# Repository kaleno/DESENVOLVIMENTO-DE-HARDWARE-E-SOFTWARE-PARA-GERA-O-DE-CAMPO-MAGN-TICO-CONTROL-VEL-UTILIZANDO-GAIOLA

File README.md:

# DESENVOLVIMENTO DE HARDWARE E SOFTWARE PARA GERAÇÃO DE CAMPO MAGNÉTICO CONTROLÁVEL

Este repositório contém o trabalho de desenvolvimento de hardware e software realizado no âmbito do Laboratório de Controle e Simulação de Sistemas Aeroespaciais (LODESTAR) da Universidade de Brasília (UnB). O objetivo principal é criar uma plataforma com interface gráfica para a geração de campo magnético controlável, direcionada para aplicações no simulador de pequenos satélites do LODESTAR.

## Visão Geral

O sistema atual do laboratório inclui uma gaiola de Helmholtz com dois pares de bobinas por eixo, uma estação de trabalho e fontes de tensão controláveis. Este projeto propõe atualizações e o desenvolvimento de novas funcionalidades para a plataforma existente.

Algumas das aplicações planejadas são:

- Reprodução do campo magnético em malha fechada utilizando o modelo International Geomagnetic Reference Field (IGRF) em conjunto com o propagador de órbita Simplified General Perturbations (SGP4).
- Reprodução dos vetores de campo magnético coletados pelos sensores do satélite AlfaCrux, recentemente lançado.
- Realização de testes preliminares para validar o novo sistema no contexto dos projetos em andamento no LODESTAR.

## Estrutura do Repositório

O repositório está organizado da seguinte forma:

- `Firmware_Circuito_Inversor/`: Contém os arquivos relacionados ao firmware do circuito inversor.
- `Outros/`: Diretório para outros arquivos relevantes.
- `PonteH/`: Contém os arquivos relacionados à ponte H.
- `PonteH2.0/`: Contém os arquivos relacionados à versão 2.0 da ponte H.
- `Software_Gaiola/`: Contém os arquivos relacionados ao software da gaiola de Helmholtz.
- `Manual_Gaiola_de_Helmholtz_(1).pdf`: Documento PDF contendo o manual da gaiola de Helmholtz.
- `README.md`: Este arquivo README com informações sobre o projeto.
- `TCC_ThiagoHenriqueFerreiradaSilva_biblioteca.pdf`: Documento PDF contendo o TCC (Trabalho de Conclusão de Curso) intitulado "DESENVOLVIMENTO DE HARDWARE E SOFTWARE PARA GERAÇÃO DE CAMPO MAGNÉTICO CONTROLÁVEL".

Certifique-se de ajustar os nomes dos diretórios e arquivos de acordo com a estrutura do seu repositório.

## Pré-requisitos e Instalação

1. Certifique-se de ter os seguintes componentes presentes no arquivo requirements.bat

2. Clone este repositório em sua máquina local usando o seguinte comando:

**git clone https://github.com/seu-usuario/nome-do-repositorio.git**

3. Navegue até o diretório clonado.

4. Siga as instruções específicas contidas em `Manual_Gaiola_de_Helmholtz_(1).pdf` para configurar e instalar as respectivas partes do sistema.

## Utilização

1. Certifique-se de que o hardware está corretamente configurado e conectado à sua estação de trabalho.

2. Inicie o software e abra a interface gráfica do sistema.

3. Utilize as funcionalidades disponíveis para gerar o campo magnético controlável de acordo com suas necessidades.

4. Consulte a documentação disponível em `docs/` para obter informações adicionais sobre a utilização do sistema.

## Contribuição

Se você deseja contribuir para este projeto, sinta-se à vontade para enviar um pull request com suas melhorias. Toda contribuição é bem-vinda!

## Licença

Este projeto é licenciado sob a MIT. Consulte o arquivo LICENSE para obter mais informações.

## Contato

Para mais informações sobre este projeto, entre em contato conosco:

- Nome: Thiago Henrique Ferreira da Silva
- E-mail: thiago.henriquef@hotmail.com

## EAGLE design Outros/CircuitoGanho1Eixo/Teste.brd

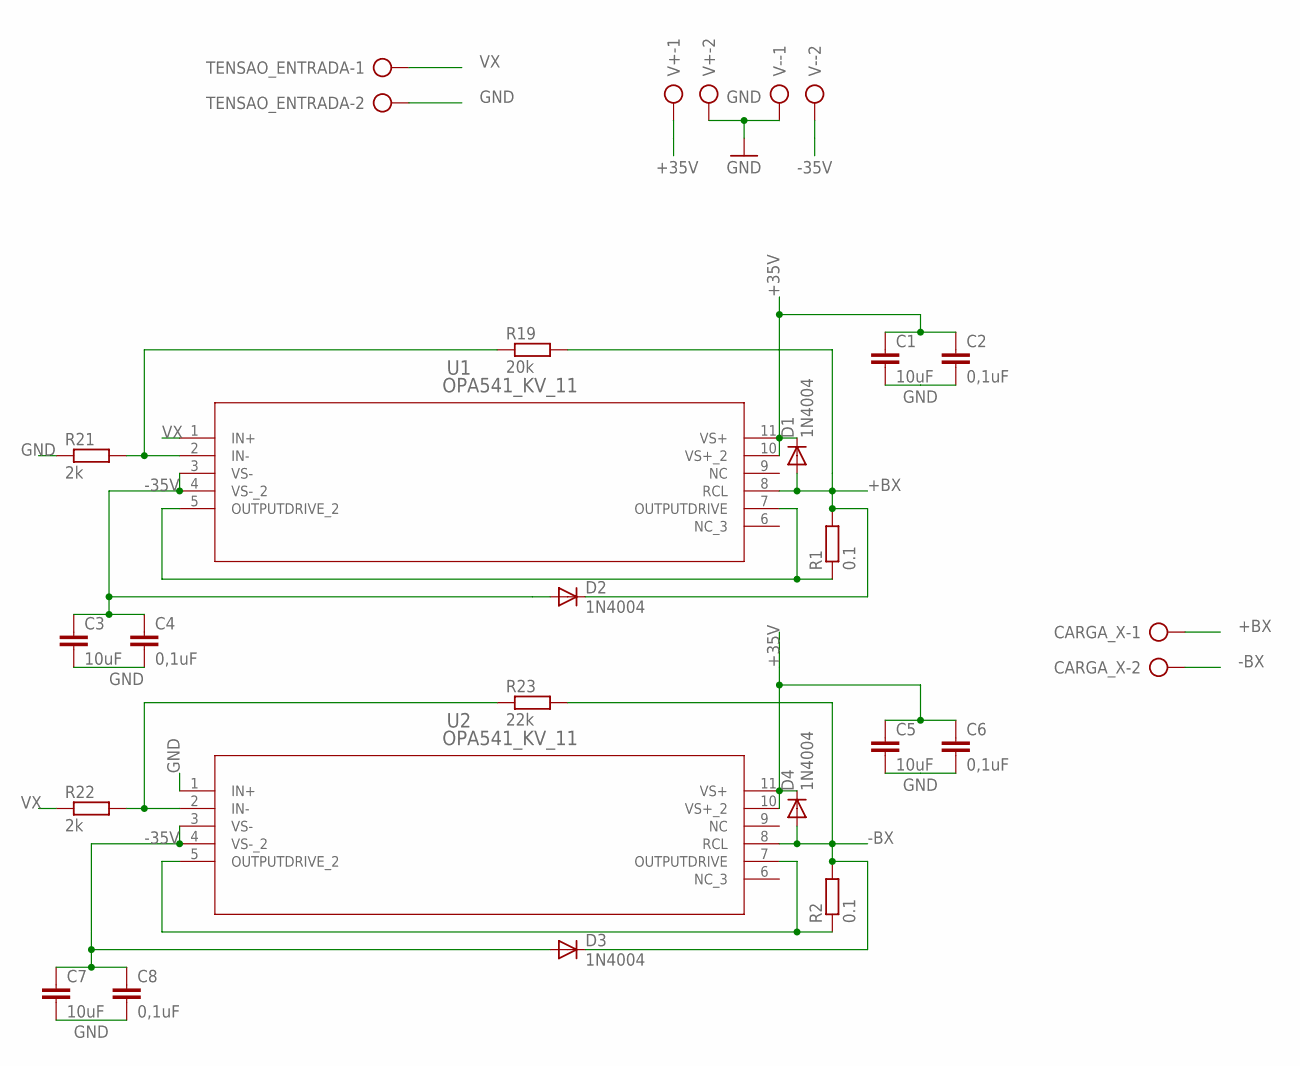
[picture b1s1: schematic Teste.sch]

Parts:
C1, C3, C5, C7: 10uF; C025-024X044
C2, C4, C6, C8: 0,1uF; C025-024X044
CARGA_X: AK500/2-H
D1, D2, D3, D4: 1N4004; DO41-10
R1, R2: 0.1; 0204/7
R19: 20k; 0207/7
R21, R22: 2k; 0207/7
R23: 22k; 0207/7
TENSAO_ENTRADA: AK500/2-H
U1, U2: OPA541_KV_11; KV11
V+: AK500/2-H
V-: AK500/2-H

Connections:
+35V: C1.1, C2.1, C5.1, C6.1, D1.C, D4.C, U1.10 (VS+_2), U1.11 (VS+), U2.10 (VS+_2), U2.11 (VS+), V+.1
+BX: CARGA_X.1, D1.A, D2.C, R1.2, R19.2, U1.8 (RCL)
-35V: C3.1, C4.1, C7.1, C8.1, D2.A, D3.A, U1.3 (VS-), U1.4 (VS-_2), U2.3 (VS-), U2.4 (VS-_2), V-.2
-BX: CARGA_X.2, D3.C, D4.A, R2.2, R23.2, U2.8 (RCL)
GND: C1.2, C2.2, C3.2, C4.2, C5.2, C6.2, C7.2, C8.2, R21.1, TENSAO_ENTRADA.2, U2.1 (IN+), V+.2, V-.1
unnamed: R19.1, R21.2, U1.2 (IN-)
unnamed: R2.1, U2.5 (OUTPUTDRIVE_2), U2.7 (OUTPUTDRIVE)
unnamed: R1.1, U1.5 (OUTPUTDRIVE_2), U1.7 (OUTPUTDRIVE)
unnamed: R22.2, R23.1, U2.2 (IN-)
VX: R22.1, TENSAO_ENTRADA.1, U1.1 (IN+)

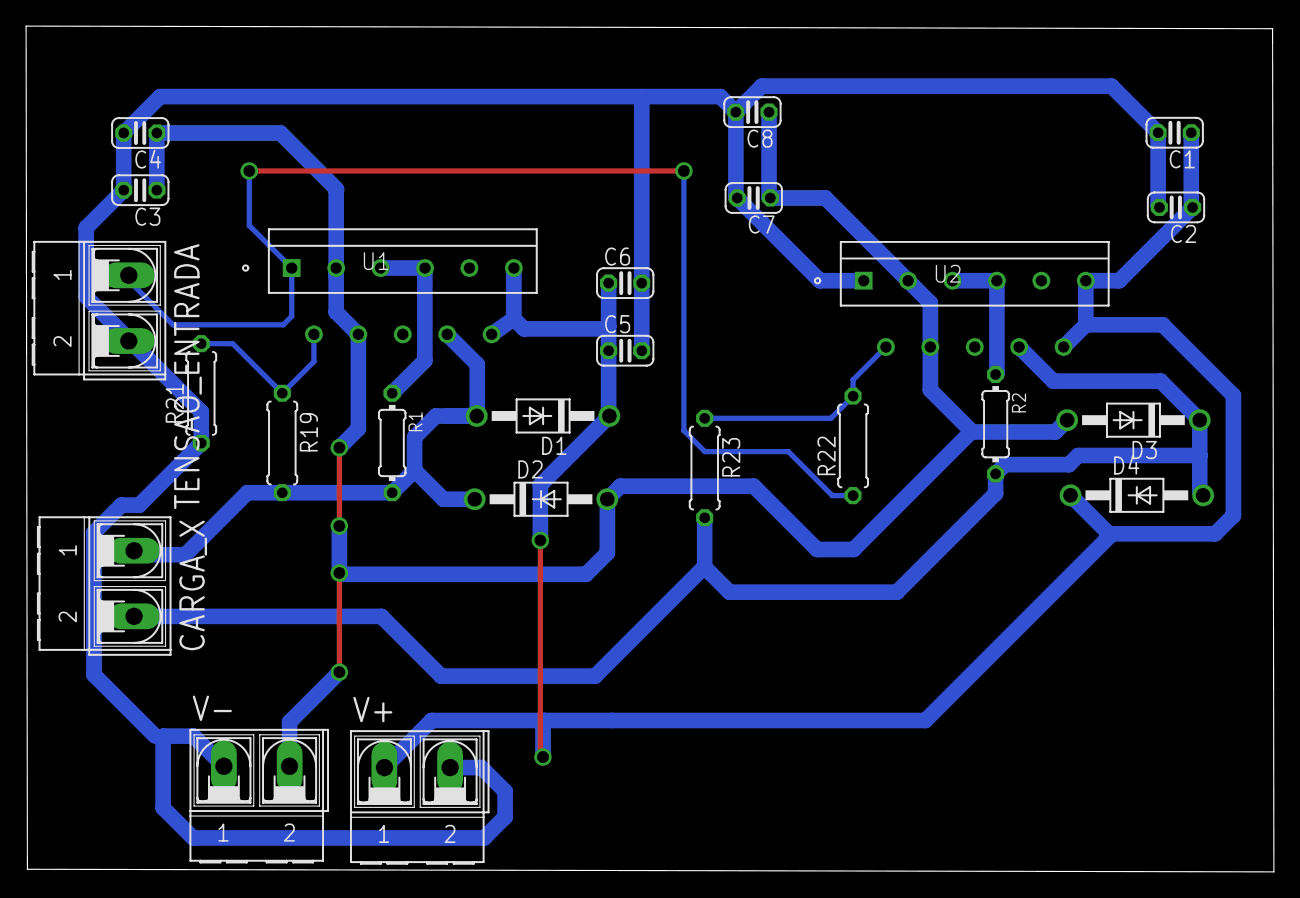
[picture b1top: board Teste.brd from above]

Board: 2 copper layers, 95.6 x 64.8 mm, 24 parts (0 on the bottom side), 10 nets.

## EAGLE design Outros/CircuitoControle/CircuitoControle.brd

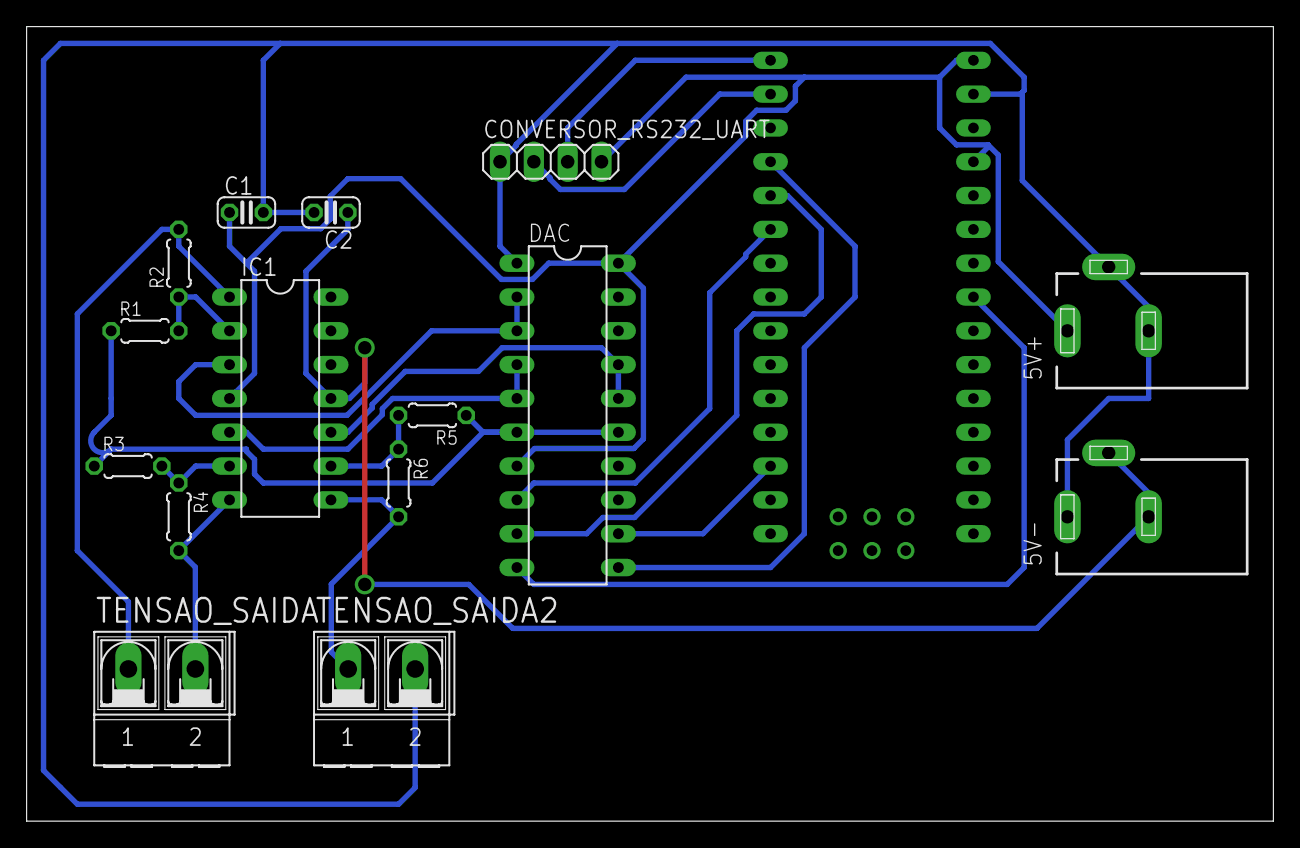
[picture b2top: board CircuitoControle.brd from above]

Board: 2 copper layers, 93.7 x 59.7 mm, 16 parts (0 on the bottom side), 19 nets.

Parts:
5V+, 5V-: DCJ0202
C1: 0,1uF; C025-024X044
C2: C025-024X044
CONVERSOR_RS232_UART: 1X04
DAC: DIL20
IC1: TL074P; DIL14
R1, R2, R3, R4, R5, R6: 10k; 0204/5
STM32: NANO
TENSAO_SAIDA, TENSAO_SAIDA2: AK500/2-H

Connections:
2,5V: DAC.6, DAC.15, R1.1, R3.1, R5.1
+5V: 5V+.1, C1.1, CONVERSOR_RS232_UART.4, DAC.7, DAC.20, IC1.4, STM32.D9
-5V: 5V-.2, 5V-.3, C2.1, IC1.11
GND: 5V+.2, 5V+.3, 5V-.1, C1.2, C2.2, CONVERSOR_RS232_UART.1, DAC.1, DAC.11, STM32.A0, STM32.D11, TENSAO_SAIDA2.2
MISO: DAC.12, STM32.RST
MOSI: DAC.9, STM32.A1
unnamed: IC1.6, R3.2, R4.1
unnamed: IC1.2, R1.2, R2.1
unnamed: IC1.9, R5.2, R6.1
OUTA: DAC.2, DAC.3, IC1.3
OUTB: DAC.4, DAC.5, IC1.5
OUTC: DAC.16, DAC.17, IC1.10
RX: CONVERSOR_RS232_UART.2, STM32.3.3V
SCK: DAC.10, STM32.D5
SS: DAC.8, STM32.A2
TX: CONVERSOR_RS232_UART.3, STM32.D13
VX: IC1.1, R2.2, TENSAO_SAIDA.1
VY: IC1.7, R4.2, TENSAO_SAIDA.2
VZ: IC1.8, R6.2, TENSAO_SAIDA2.1

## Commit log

2023-01-28 Add files via upload
    Versão mais lenta e mais estável
